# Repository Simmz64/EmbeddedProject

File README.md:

# EmbeddedProject
Project course in embedded systems

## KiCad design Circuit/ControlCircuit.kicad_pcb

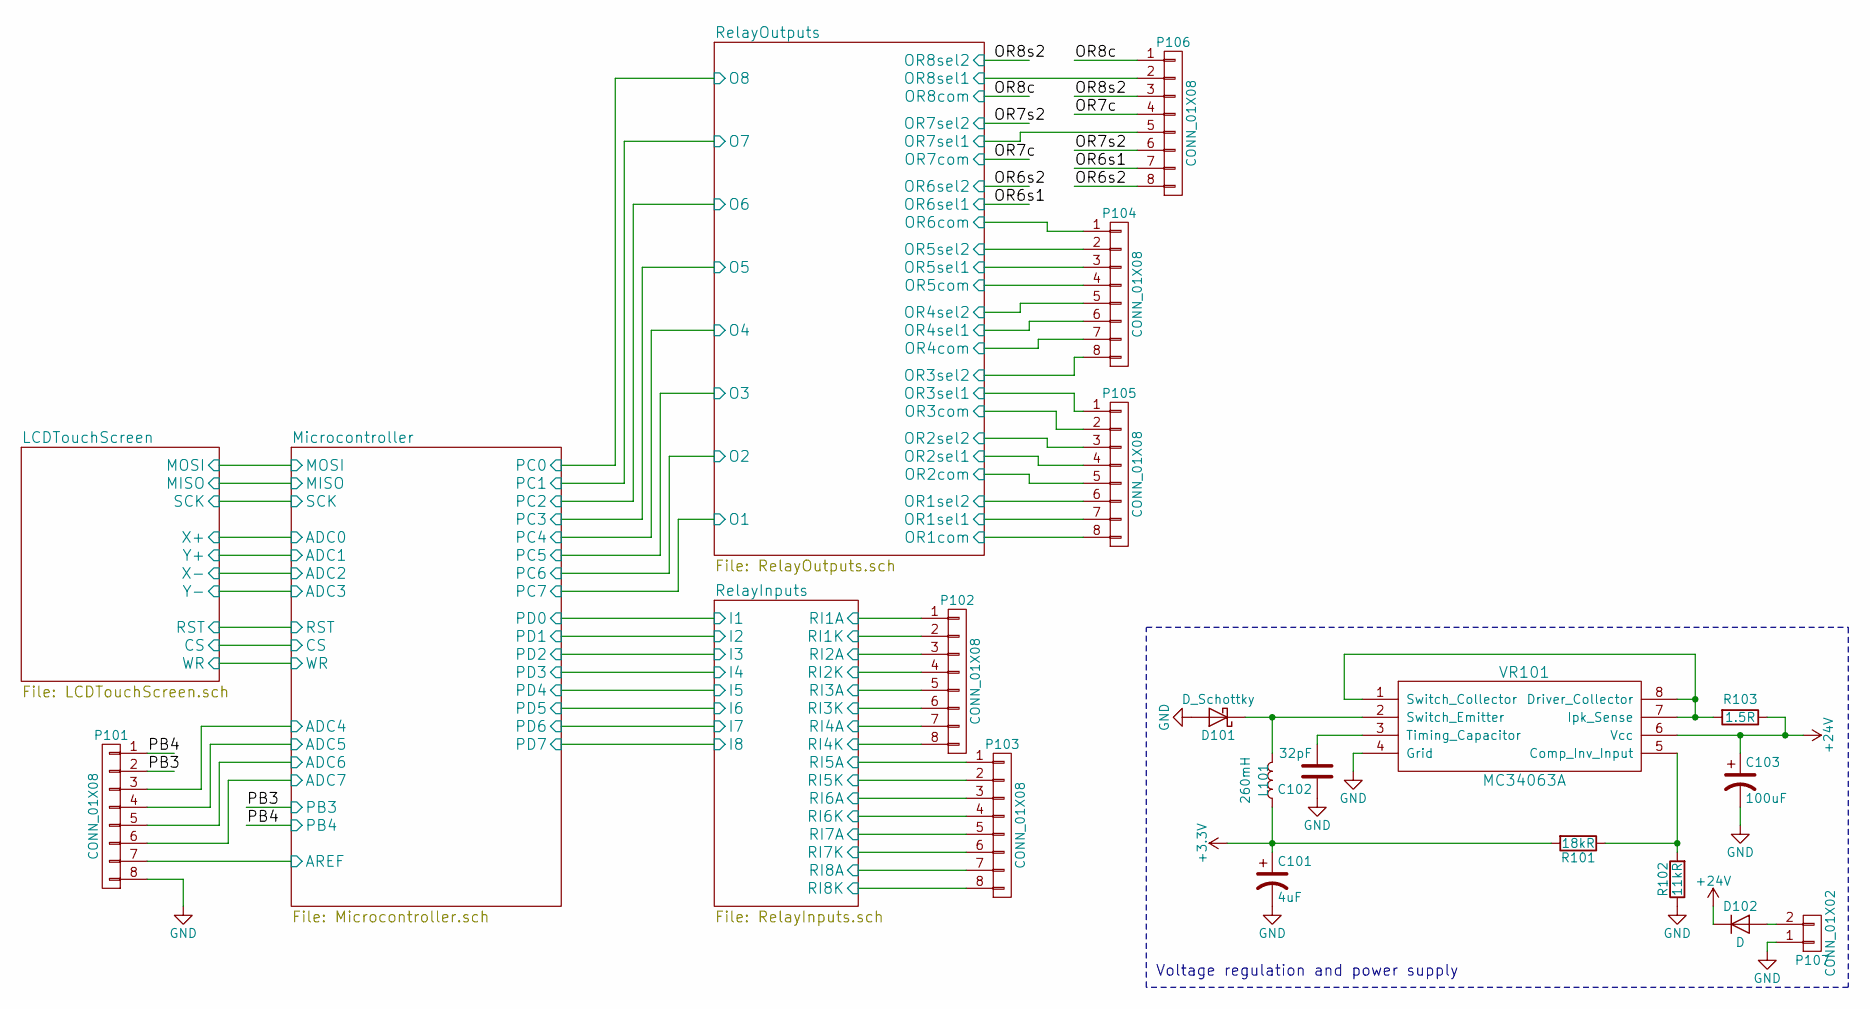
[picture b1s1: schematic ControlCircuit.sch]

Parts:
C101: 4uF; C_1206
C102: 32pF; C_0805
C103: 100uF; C_0805
D101: D_Schottky; D_MiniMELF_Standard
D102: D; D_MELF_Standard
L101: 260mH; Inductor_Wurth_HCI-7050
P101, P102, P103, P104, P105, P106: CONN_01X08; TerminalBlock_Pheonix_MKDS1.5-8pol
P107: CONN_01X02; TerminalBlock_Pheonix_MKDS1.5-2pol
R101: 18kR; R_0805
R102: 11kR; R_0805
R103: 1.5R; R_0805
VR101: MC34063A; SOIC-8_3.9x4.9mm_Pitch1.27mm

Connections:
+3V3: C101.1, L101.1, R101.2; also elsewhere on the board
+24V: C103.1, D102.1 (K), R103.1, VR101.6 (Vcc); also elsewhere on the board
/Microcontroller/ADC4: P101.3; also elsewhere on the board
/Microcontroller/ADC5: P101.4; also elsewhere on the board
/Microcontroller/ADC6: P101.5; also elsewhere on the board
/Microcontroller/ADC7: P101.6; also elsewhere on the board
/Microcontroller/AREF: P101.7; also elsewhere on the board
/OR6s1: P106.7; also elsewhere on the board
/OR6s2: P106.8; also elsewhere on the board
/OR7c: P106.4; also elsewhere on the board
/OR7s2: P106.6; also elsewhere on the board
/OR8c: P106.1; also elsewhere on the board
/OR8s2: P106.3; also elsewhere on the board
/PB3: P101.2; also elsewhere on the board
/PB4: P101.1; also elsewhere on the board
/RelayInputs/RI1A: P102.1; also elsewhere on the board
/RelayInputs/RI1K: P102.2; also elsewhere on the board
/RelayInputs/RI2A: P102.3; also elsewhere on the board
/RelayInputs/RI2K: P102.4; also elsewhere on the board
/RelayInputs/RI3A: P102.5; also elsewhere on the board
/RelayInputs/RI3K: P102.6; also elsewhere on the board
/RelayInputs/RI4A: P102.7; also elsewhere on the board
/RelayInputs/RI4K: P102.8; also elsewhere on the board
/RelayInputs/RI5A: P103.1; also elsewhere on the board
/RelayInputs/RI5K: P103.2; also elsewhere on the board
/RelayInputs/RI6A: P103.3; also elsewhere on the board
/RelayInputs/RI6K: P103.4; also elsewhere on the board
/RelayInputs/RI7A: P103.5; also elsewhere on the board
/RelayInputs/RI7K: P103.6; also elsewhere on the board
/RelayInputs/RI8A: P103.7; also elsewhere on the board
/RelayInputs/RI8K: P103.8; also elsewhere on the board
/RelayOutputs/OR1com: P105.8; also elsewhere on the board
/RelayOutputs/OR1sel1: P105.7; also elsewhere on the board
/RelayOutputs/OR1sel2: P105.6; also elsewhere on the board
/RelayOutputs/OR2com: P105.5; also elsewhere on the board
/RelayOutputs/OR2sel1: P105.4; also elsewhere on the board
/RelayOutputs/OR2sel2: P105.3; also elsewhere on the board
/RelayOutputs/OR3com: P105.2; also elsewhere on the board
/RelayOutputs/OR3sel1: P105.1; also elsewhere on the board
/RelayOutputs/OR3sel2: P104.8; also elsewhere on the board
/RelayOutputs/OR4com: P104.7; also elsewhere on the board
/RelayOutputs/OR4sel1: P104.6; also elsewhere on the board
/RelayOutputs/OR4sel2: P104.5; also elsewhere on the board
/RelayOutputs/OR5com: P104.4; also elsewhere on the board
/RelayOutputs/OR5sel1: P104.3; also elsewhere on the board
/RelayOutputs/OR5sel2: P104.2; also elsewhere on the board
/RelayOutputs/OR6com: P104.1; also elsewhere on the board
/RelayOutputs/OR7sel1: P106.5; also elsewhere on the board
/RelayOutputs/OR8sel1: P106.2; also elsewhere on the board
GND: C101.2, C102.1, C103.2, D101.2 (A), P101.8, P107.1, R102.1, VR101.4 (Grid); also elsewhere on the board
unnamed: C102.2, VR101.3 (Timing_Capacitor)
unnamed: D101.1 (K), L101.2, VR101.2 (Switch_Emitter)
unnamed: D102.2 (A), P107.2
unnamed: R101.1, R102.2, VR101.5 (Comp_Inv_Input)
unnamed: R103.2, VR101.1 (Switch_Collector), VR101.7 (Ipk_Sense), VR101.8 (Driver_Collector)

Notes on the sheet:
Voltage regulation and power supply

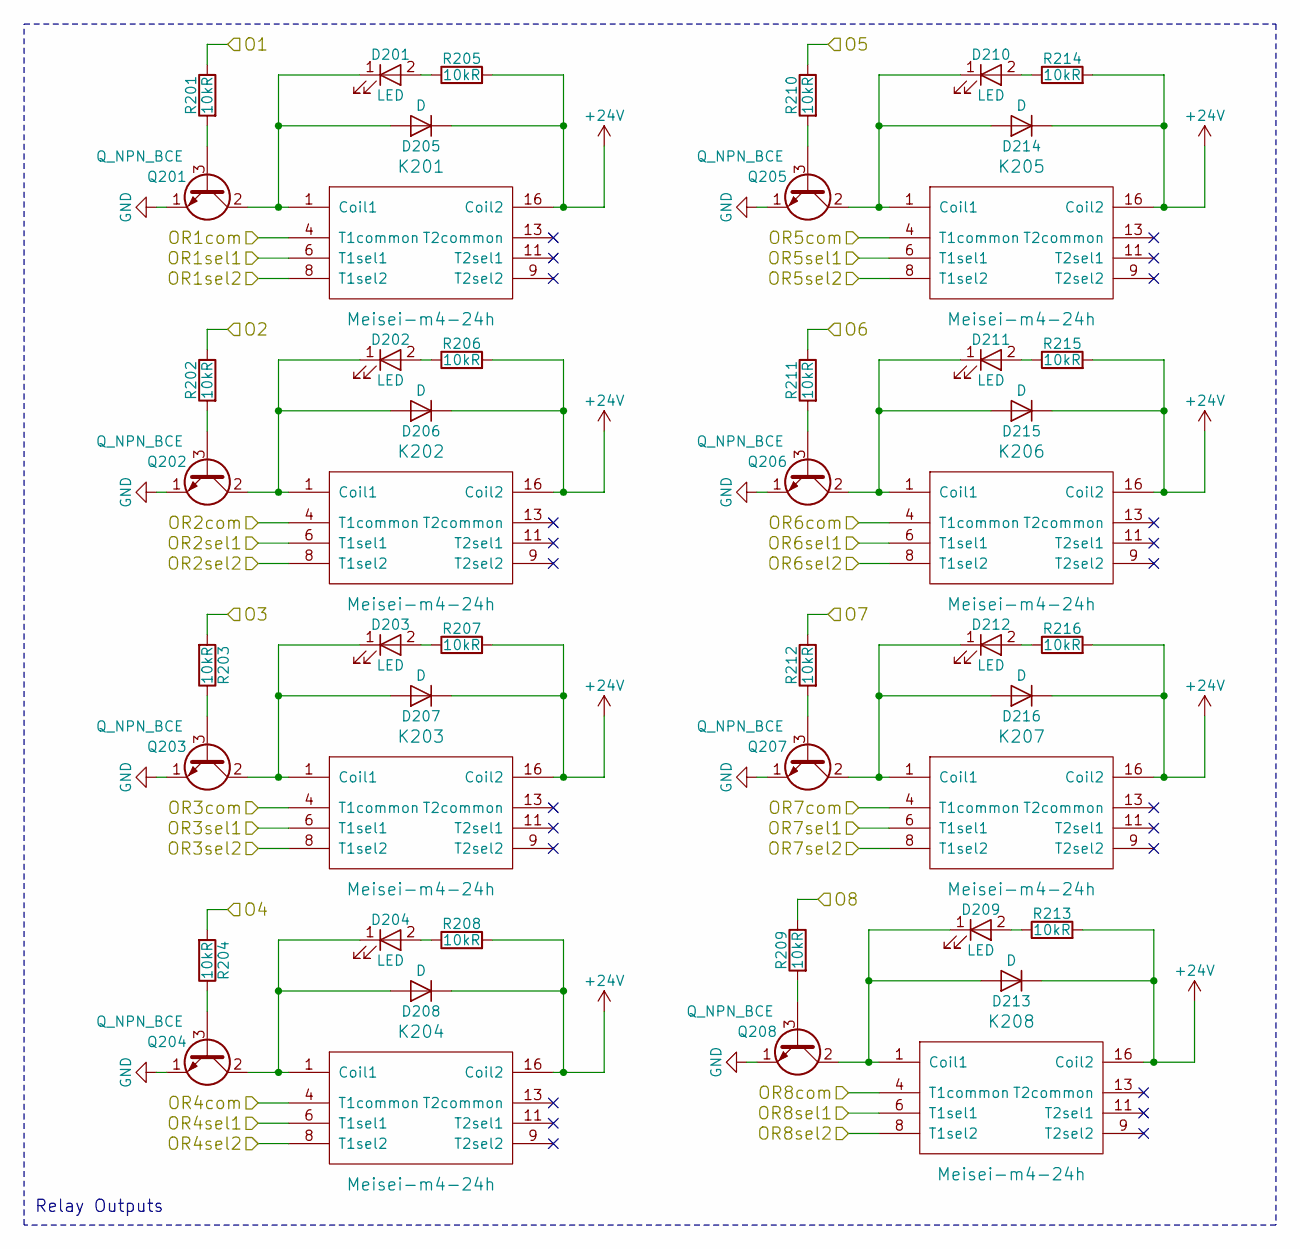
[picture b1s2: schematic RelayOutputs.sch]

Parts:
D201, D202, D203, D204, D209, D210, D211, D212: LED; C_0805
D205, D206, D207, D208, D213, D214, D215, D216: D; D_MiniMELF_Standard
K201, K202, K203, K204, K205, K206, K207, K208: Meisei-m4-24h
Q201, Q202, Q203, Q204, Q205, Q206, Q207, Q208: Q_NPN_BCE; MMBT3904
R201, R202, R203, R204, R205, R206, R207, R208, R209, R210, R211, R212, R213, R214, R215, R216: 10kR; R_0805

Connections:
+24V: D205.1 (K), D206.1 (K), D207.1 (K), D208.1 (K), D213.1 (K), D214.1 (K), D215.1 (K), D216.1 (K), K201.16 (Coil2), K202.16 (Coil2), K203.16 (Coil2), K204.16 (Coil2), K205.16 (Coil2), K206.16 (Coil2), K207.16 (Coil2), K208.16 (Coil2), R205.2, R206.2, R207.2, R208.2, R213.2, R214.2, R215.2, R216.2; also elsewhere on the board
/OR6s1: K206.6 (T1sel1); also elsewhere on the board
/OR6s2: K206.8 (T1sel2); also elsewhere on the board
/OR7c: K207.4 (T1common); also elsewhere on the board
/OR7s2: K207.8 (T1sel2); also elsewhere on the board
/OR8c: K208.4 (T1common); also elsewhere on the board
/OR8s2: K208.8 (T1sel2); also elsewhere on the board
/RelayOutputs/O1: R201.1; also elsewhere on the board
/RelayOutputs/O2: R202.1; also elsewhere on the board
/RelayOutputs/O3: R203.2; also elsewhere on the board
/RelayOutputs/O4: R204.2; also elsewhere on the board
/RelayOutputs/O5: R210.1; also elsewhere on the board
/RelayOutputs/O6: R211.1; also elsewhere on the board
/RelayOutputs/O7: R212.1; also elsewhere on the board
/RelayOutputs/O8: R209.1; also elsewhere on the board
/RelayOutputs/OR1com: K201.4 (T1common); also elsewhere on the board
/RelayOutputs/OR1sel1: K201.6 (T1sel1); also elsewhere on the board
/RelayOutputs/OR1sel2: K201.8 (T1sel2); also elsewhere on the board
/RelayOutputs/OR2com: K202.4 (T1common); also elsewhere on the board
/RelayOutputs/OR2sel1: K202.6 (T1sel1); also elsewhere on the board
/RelayOutputs/OR2sel2: K202.8 (T1sel2); also elsewhere on the board
/RelayOutputs/OR3com: K203.4 (T1common); also elsewhere on the board
/RelayOutputs/OR3sel1: K203.6 (T1sel1); also elsewhere on the board
/RelayOutputs/OR3sel2: K203.8 (T1sel2); also elsewhere on the board
/RelayOutputs/OR4com: K204.4 (T1common); also elsewhere on the board
/RelayOutputs/OR4sel1: K204.6 (T1sel1); also elsewhere on the board
/RelayOutputs/OR4sel2: K204.8 (T1sel2); also elsewhere on the board
/RelayOutputs/OR5com: K205.4 (T1common); also elsewhere on the board
/RelayOutputs/OR5sel1: K205.6 (T1sel1); also elsewhere on the board
/RelayOutputs/OR5sel2: K205.8 (T1sel2); also elsewhere on the board
/RelayOutputs/OR6com: K206.4 (T1common); also elsewhere on the board
/RelayOutputs/OR7sel1: K207.6 (T1sel1); also elsewhere on the board
/RelayOutputs/OR8sel1: K208.6 (T1sel1); also elsewhere on the board
GND: Q201.1 (E), Q202.1 (E), Q203.1 (E), Q204.1 (E), Q205.1 (E), Q206.1 (E), Q207.1 (E), Q208.1 (E); also elsewhere on the board
unnamed: D201.1 (K), D205.2 (A), K201.1 (Coil1), Q201.2 (C)
unnamed: D201.2 (A), R205.1
unnamed: D202.1 (K), D206.2 (A), K202.1 (Coil1), Q202.2 (C)
unnamed: D202.2 (A), R206.1
unnamed: D203.1 (K), D207.2 (A), K203.1 (Coil1), Q203.2 (C)
unnamed: D203.2 (A), R207.1
unnamed: D204.1 (K), D208.2 (A), K204.1 (Coil1), Q204.2 (C)
unnamed: D204.2 (A), R208.1
unnamed: D209.1 (K), D213.2 (A), K208.1 (Coil1), Q208.2 (C)
unnamed: D209.2 (A), R213.1
unnamed: D210.1 (K), D214.2 (A), K205.1 (Coil1), Q205.2 (C)
unnamed: D210.2 (A), R214.1
unnamed: D211.1 (K), D215.2 (A), K206.1 (Coil1), Q206.2 (C)
unnamed: D211.2 (A), R215.1
unnamed: D212.1 (K), D216.2 (A), K207.1 (Coil1), Q207.2 (C)
unnamed: D212.2 (A), R216.1
unnamed: Q201.3 (B), R201.2
unnamed: Q202.3 (B), R202.2
unnamed: Q203.3 (B), R203.1
unnamed: Q204.3 (B), R204.1
unnamed: Q205.3 (B), R210.2
unnamed: Q206.3 (B), R211.2
unnamed: Q207.3 (B), R212.2
unnamed: Q208.3 (B), R209.2

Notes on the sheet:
Relay Outputs

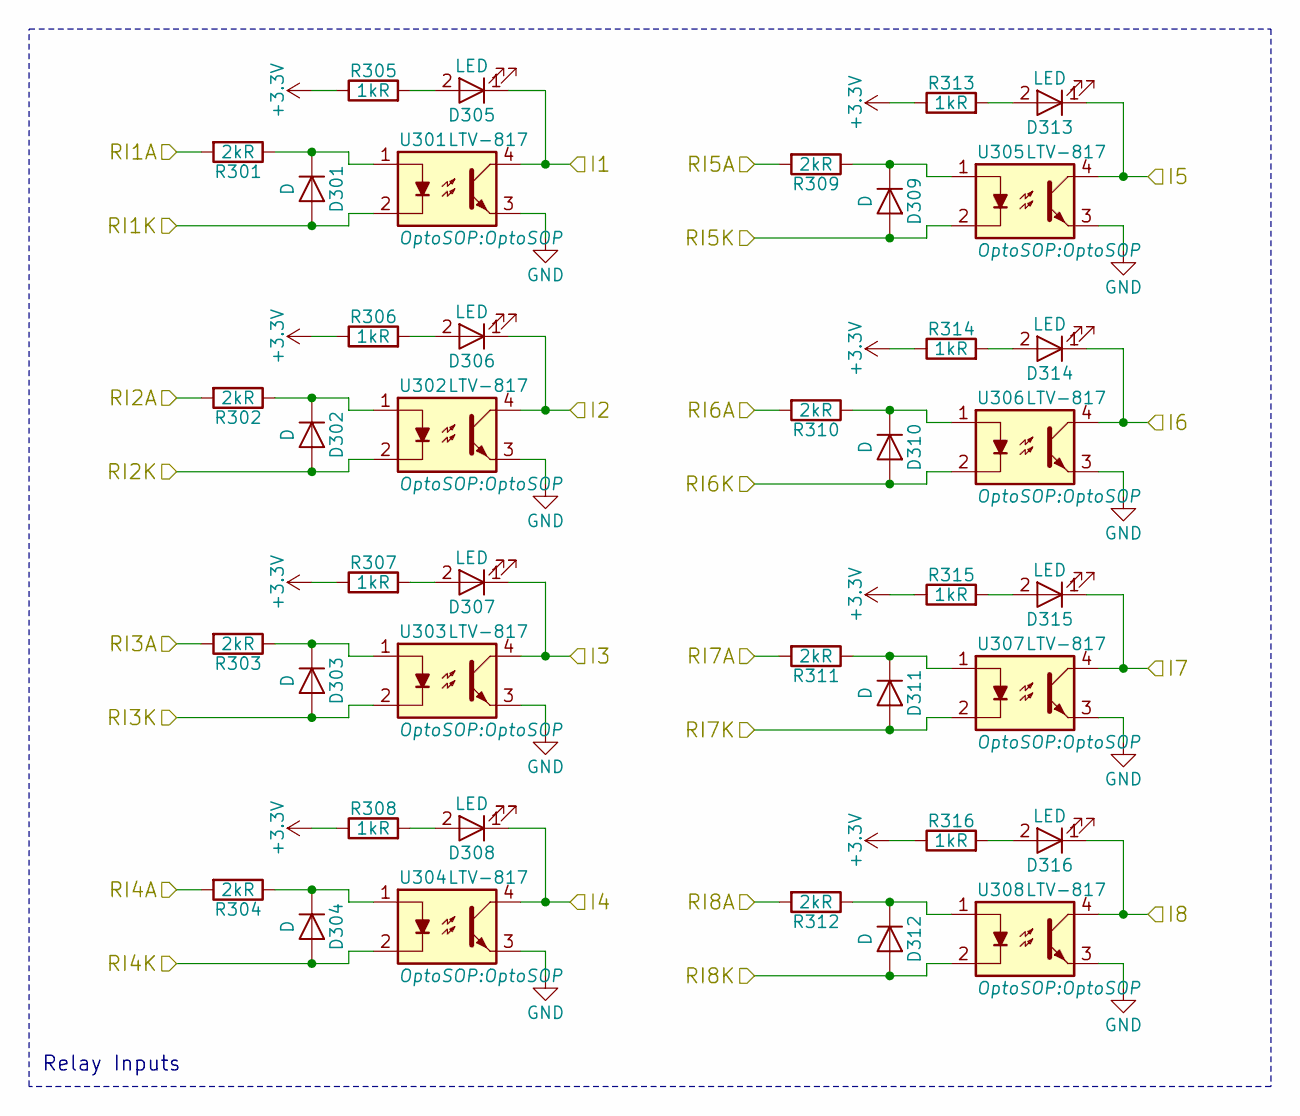
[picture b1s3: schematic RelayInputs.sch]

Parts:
D301, D302, D303, D304, D309, D310, D311, D312: D; D_MiniMELF_Standard
D305, D306, D307, D308, D313, D314, D315, D316: LED; C_0805
R301, R302, R303, R304, R309, R310, R311, R312: 2kR; R_0805
R305, R306, R307, R308, R313, R314, R315, R316: 1kR; R_0805
U301, U302, U303, U304, U305, U306, U307, U308: LTV-817; OptoSOP

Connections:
+3V3: R305.1, R306.1, R307.1, R308.1, R313.1, R314.1, R315.1, R316.1; also elsewhere on the board
/RelayInputs/I1: D305.1 (K), U301.4; also elsewhere on the board
/RelayInputs/I2: D306.1 (K), U302.4; also elsewhere on the board
/RelayInputs/I3: D307.1 (K), U303.4; also elsewhere on the board
/RelayInputs/I4: D308.1 (K), U304.4; also elsewhere on the board
/RelayInputs/I5: D313.1 (K), U305.4; also elsewhere on the board
/RelayInputs/I6: D314.1 (K), U306.4; also elsewhere on the board
/RelayInputs/I7: D315.1 (K), U307.4; also elsewhere on the board
/RelayInputs/I8: D316.1 (K), U308.4; also elsewhere on the board
/RelayInputs/RI1A: R301.2; also elsewhere on the board
/RelayInputs/RI1K: D301.2 (A), U301.2; also elsewhere on the board
/RelayInputs/RI2A: R302.2; also elsewhere on the board
/RelayInputs/RI2K: D302.2 (A), U302.2; also elsewhere on the board
/RelayInputs/RI3A: R303.2; also elsewhere on the board
/RelayInputs/RI3K: D303.2 (A), U303.2; also elsewhere on the board
/RelayInputs/RI4A: R304.2; also elsewhere on the board
/RelayInputs/RI4K: D304.2 (A), U304.2; also elsewhere on the board
/RelayInputs/RI5A: R309.2; also elsewhere on the board
/RelayInputs/RI5K: D309.2 (A), U305.2; also elsewhere on the board
/RelayInputs/RI6A: R310.2; also elsewhere on the board
/RelayInputs/RI6K: D310.2 (A), U306.2; also elsewhere on the board
/RelayInputs/RI7A: R311.2; also elsewhere on the board
/RelayInputs/RI7K: D311.2 (A), U307.2; also elsewhere on the board
/RelayInputs/RI8A: R312.2; also elsewhere on the board
/RelayInputs/RI8K: D312.2 (A), U308.2; also elsewhere on the board
GND: U301.3, U302.3, U303.3, U304.3, U305.3, U306.3, U307.3, U308.3; also elsewhere on the board
unnamed: D301.1 (K), R301.1, U301.1
unnamed: D302.1 (K), R302.1, U302.1
unnamed: D303.1 (K), R303.1, U303.1
unnamed: D304.1 (K), R304.1, U304.1
unnamed: D305.2 (A), R305.2
unnamed: D306.2 (A), R306.2
unnamed: D307.2 (A), R307.2
unnamed: D308.2 (A), R308.2
unnamed: D309.1 (K), R309.1, U305.1
unnamed: D310.1 (K), R310.1, U306.1
unnamed: D311.1 (K), R311.1, U307.1
unnamed: D312.1 (K), R312.1, U308.1
unnamed: D313.2 (A), R313.2
unnamed: D314.2 (A), R314.2
unnamed: D315.2 (A), R315.2
unnamed: D316.2 (A), R316.2

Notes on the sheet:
Relay Inputs

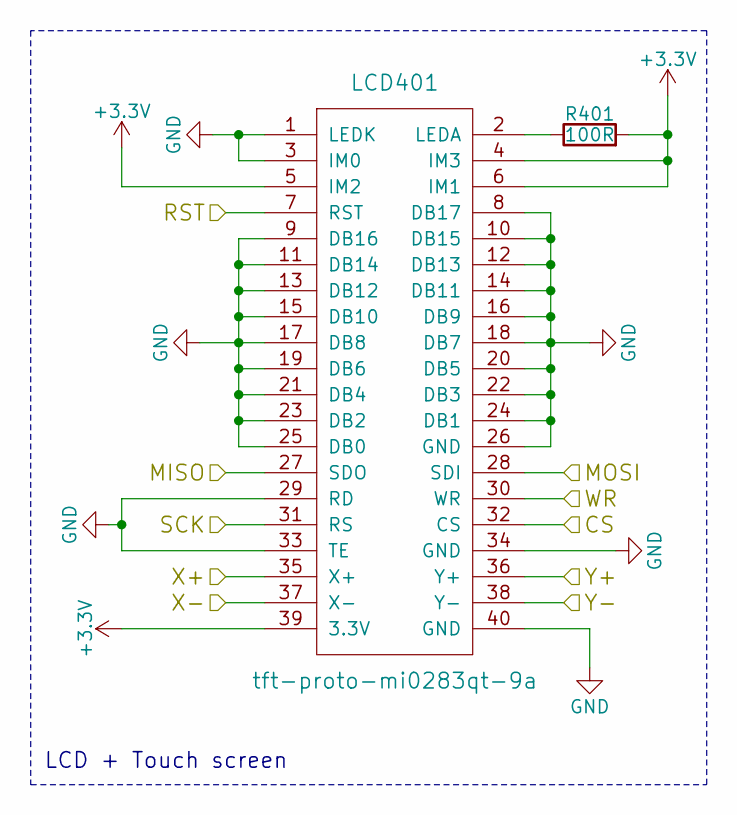
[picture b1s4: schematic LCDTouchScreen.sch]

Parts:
LCD401: tft-proto-mi0283qt-9a; Pin_Header_Straight_2x20_Pitch2.54mm
R401: 100R; R_0805

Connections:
+3V3: LCD401.4 (IM3), LCD401.5 (IM2), LCD401.6 (IM1), LCD401.39 (3.3V), R401.2; also elsewhere on the board
/LCDTouchScreen/CS: LCD401.32 (CS); also elsewhere on the board
/LCDTouchScreen/MISO: LCD401.27 (SDO); also elsewhere on the board
/LCDTouchScreen/MOSI: LCD401.28 (SDI); also elsewhere on the board
/LCDTouchScreen/RST: LCD401.7 (RST); also elsewhere on the board
/LCDTouchScreen/SCK: LCD401.31 (RS); also elsewhere on the board
/LCDTouchScreen/WR: LCD401.30 (WR); also elsewhere on the board
/Microcontroller/ADC0: LCD401.35 (X+); also elsewhere on the board
/Microcontroller/ADC1: LCD401.36 (Y+); also elsewhere on the board
/Microcontroller/ADC2: LCD401.37 (X-); also elsewhere on the board
/Microcontroller/ADC3: LCD401.38 (Y-); also elsewhere on the board
GND: LCD401.1 (LEDK), LCD401.3 (IM0), LCD401.8 (DB17), LCD401.9 (DB16), LCD401.10 (DB15), LCD401.11 (DB14), LCD401.12 (DB13), LCD401.13 (DB12), LCD401.14 (DB11), LCD401.15 (DB10), LCD401.16 (DB9), LCD401.17 (DB8), LCD401.18 (DB7), LCD401.19 (DB6), LCD401.20 (DB5), LCD401.21 (DB4), LCD401.22 (DB3), LCD401.23 (DB2), LCD401.24 (DB1), LCD401.25 (DB0), LCD401.26 (GND), LCD401.29 (RD), LCD401.33 (TE), LCD401.34 (GND), LCD401.40 (GND); also elsewhere on the board
unnamed: LCD401.2 (LEDA), R401.1

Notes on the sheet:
LCD + Touch screen

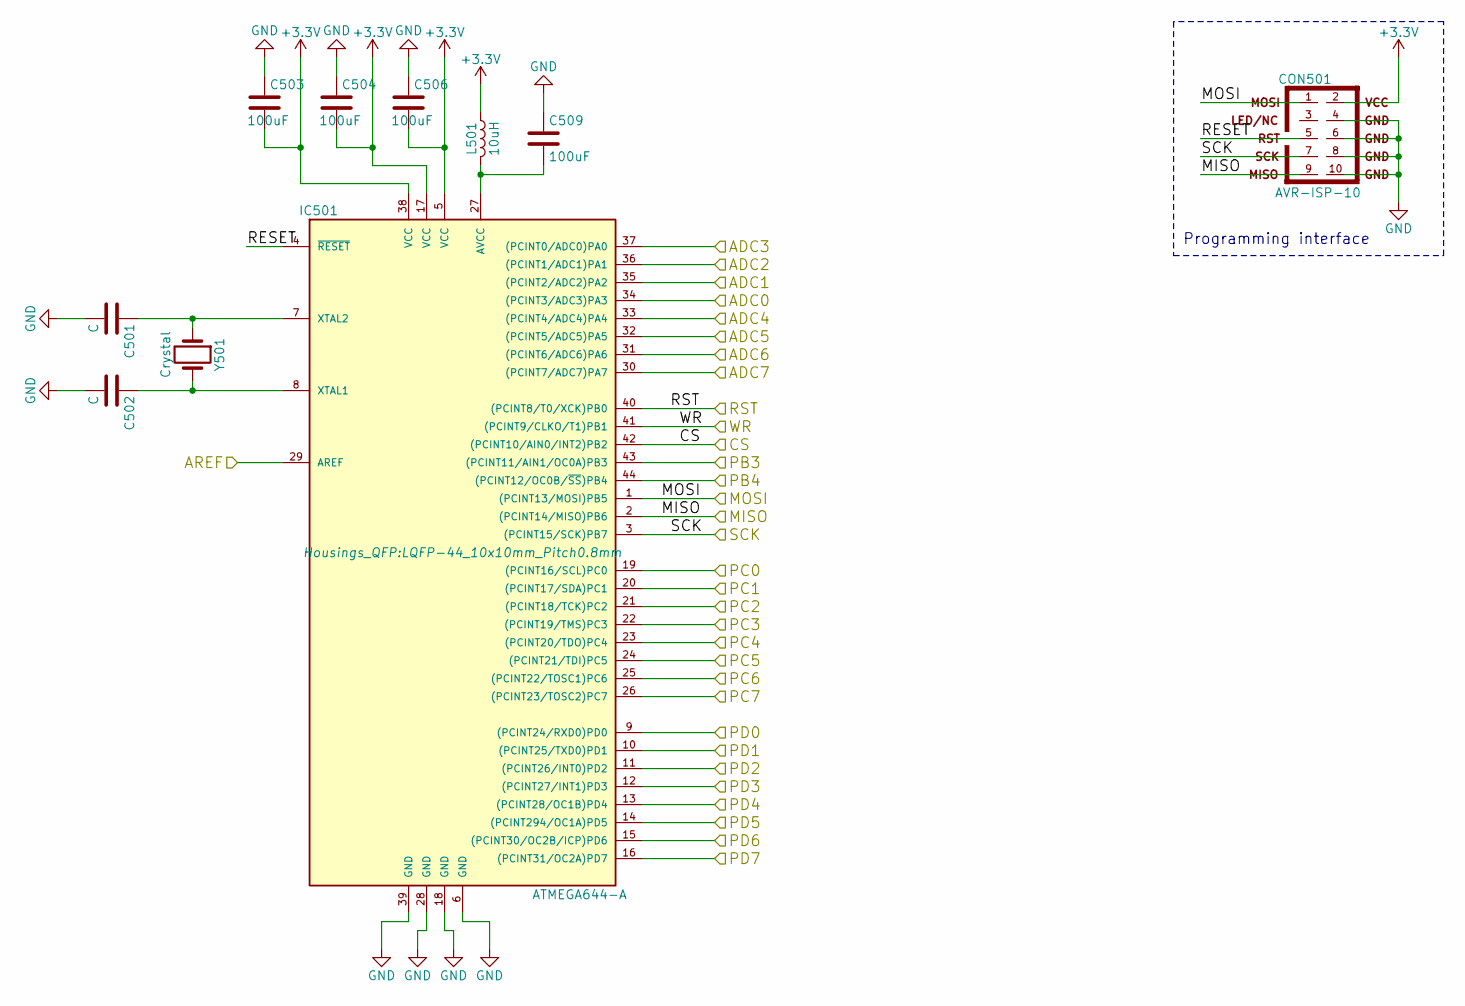
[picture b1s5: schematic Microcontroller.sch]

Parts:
C501, C502: C; C_0805
C503, C504, C506, C509: 100uF; C_0805
CON501: AVR-ISP-10; IDC_Header_Straight_10pins
IC501: ATMEGA644-A; LQFP-44_10x10mm_Pitch0.8mm
L501: 10uH; C_1206
Y501: Crystal; Crystal_HC49-U_Vertical

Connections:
+3V3: C503.2, C504.2, C506.2, CON501.2, IC501.5 (VCC), IC501.17 (VCC), IC501.38 (VCC), L501.1; also elsewhere on the board
/LCDTouchScreen/CS: IC501.42 ((PCINT10/AIN0/INT2)PB2); also elsewhere on the board
/LCDTouchScreen/MISO: CON501.9, IC501.2 ((PCINT14/MISO)PB6); also elsewhere on the board
/LCDTouchScreen/MOSI: CON501.1, IC501.1 ((PCINT13/MOSI)PB5); also elsewhere on the board
/LCDTouchScreen/RST: IC501.40 ((PCINT8/T0/XCK)PB0); also elsewhere on the board
/LCDTouchScreen/SCK: CON501.7, IC501.3 ((PCINT15/SCK)PB7); also elsewhere on the board
/LCDTouchScreen/WR: IC501.41 ((PCINT9/CLKO/T1)PB1); also elsewhere on the board
/Microcontroller/ADC0: IC501.34 ((PCINT3/ADC3)PA3); also elsewhere on the board
/Microcontroller/ADC1: IC501.35 ((PCINT2/ADC2)PA2); also elsewhere on the board
/Microcontroller/ADC2: IC501.36 ((PCINT1/ADC1)PA1); also elsewhere on the board
/Microcontroller/ADC3: IC501.37 ((PCINT0/ADC0)PA0); also elsewhere on the board
/Microcontroller/ADC4: IC501.33 ((PCINT4/ADC4)PA4); also elsewhere on the board
/Microcontroller/ADC5: IC501.32 ((PCINT5/ADC5)PA5); also elsewhere on the board
/Microcontroller/ADC6: IC501.31 ((PCINT6/ADC6)PA6); also elsewhere on the board
/Microcontroller/ADC7: IC501.30 ((PCINT7/ADC7)PA7); also elsewhere on the board
/Microcontroller/AREF: IC501.29 (AREF); also elsewhere on the board
/Microcontroller/RESET: CON501.5, IC501.4 (~RESET)
/PB3: IC501.43 ((PCINT11/AIN1/OC0A)PB3); also elsewhere on the board
/PB4: IC501.44 ((PCINT12/OC0B/~SS~)PB4); also elsewhere on the board
/RelayInputs/I1: IC501.9 ((PCINT24/RXD0)PD0); also elsewhere on the board
/RelayInputs/I2: IC501.10 ((PCINT25/TXD0)PD1); also elsewhere on the board
/RelayInputs/I3: IC501.11 ((PCINT26/INT0)PD2); also elsewhere on the board
/RelayInputs/I4: IC501.12 ((PCINT27/INT1)PD3); also elsewhere on the board
/RelayInputs/I5: IC501.13 ((PCINT28/OC1B)PD4); also elsewhere on the board
/RelayInputs/I6: IC501.14 ((PCINT294/OC1A)PD5); also elsewhere on the board
/RelayInputs/I7: IC501.15 ((PCINT30/OC2B/ICP)PD6); also elsewhere on the board
/RelayInputs/I8: IC501.16 ((PCINT31/OC2A)PD7); also elsewhere on the board
/RelayOutputs/O1: IC501.26 ((PCINT23/TOSC2)PC7); also elsewhere on the board
/RelayOutputs/O2: IC501.25 ((PCINT22/TOSC1)PC6); also elsewhere on the board
/RelayOutputs/O3: IC501.24 ((PCINT21/TDI)PC5); also elsewhere on the board
/RelayOutputs/O4: IC501.23 ((PCINT20/TDO)PC4); also elsewhere on the board
/RelayOutputs/O5: IC501.22 ((PCINT19/TMS)PC3); also elsewhere on the board
/RelayOutputs/O6: IC501.21 ((PCINT18/TCK)PC2); also elsewhere on the board
/RelayOutputs/O7: IC501.20 ((PCINT17/SDA)PC1); also elsewhere on the board
/RelayOutputs/O8: IC501.19 ((PCINT16/SCL)PC0); also elsewhere on the board
GND: C501.2, C502.2, C503.1, C504.1, C506.1, C509.1, CON501.4, CON501.6, CON501.8, CON501.10, IC501.6 (GND), IC501.18 (GND), IC501.28 (GND), IC501.39 (GND); also elsewhere on the board
unnamed: C501.1, IC501.7 (XTAL2), Y501.1
unnamed: C502.1, IC501.8 (XTAL1), Y501.2
unnamed: C509.2, IC501.27 (AVCC), L501.2

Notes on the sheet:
Programming interface

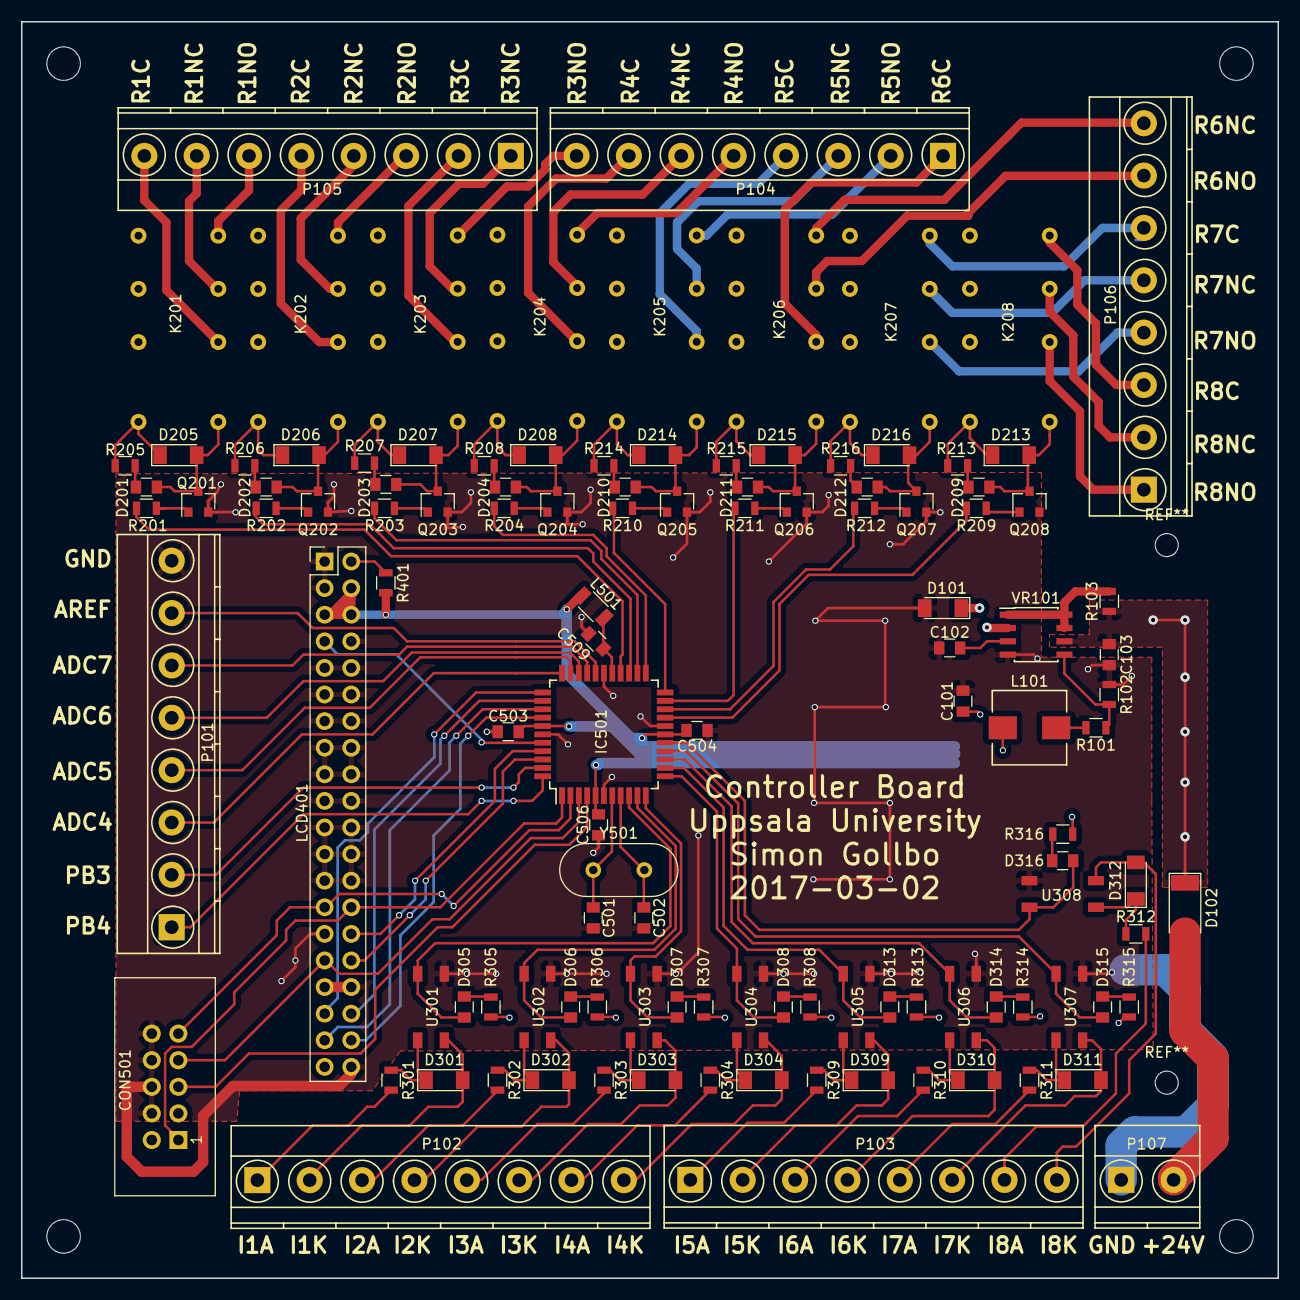
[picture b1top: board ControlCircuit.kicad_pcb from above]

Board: 2 copper layers, 120.0 x 120.0 mm, 117 parts (0 on the bottom side), 126 nets.

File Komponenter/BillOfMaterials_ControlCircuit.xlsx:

comp_id | value | footprint | tstamp | ref | Antal | Komponent | Antal | Kommentar
5 | 32pF | Capacitors_SMD:C_0805 | 58ADC3B5 | C102 | 1 | Capacitors_SMD:C_0805 | 25
7 | 4uF | Capacitors_SMD:C_0805 | 58ADC46F | C101 | 1 | Capacitors_SMD:C_1206 | 1
8 | 100uF | Capacitors_SMD:C_0805 | 58ADC4C2 | C103 | 1 | Connectors:IDC_Header_Straight_10pins | 1
50 | LED | Capacitors_SMD:C_0805 | 58B75E5F | D209 |  | Connectors_Terminal_Blocks:TerminalBlock_Pheonix_MKDS1.5-2pol | 1
52 | LED | Capacitors_SMD:C_0805 | 58B77770 | D212 |  | Connectors_Terminal_Blocks:TerminalBlock_Pheonix_MKDS1.5-8pol | 6
54 | LED | Capacitors_SMD:C_0805 | 58B79DE6 | D204 |  | Crystals:Crystal_HC49-U_Vertical | 1
56 | LED | Capacitors_SMD:C_0805 | 58B79F0F | D203 |  | Diodes_SMD:D_MELF_Standard | 1
58 | LED | Capacitors_SMD:C_0805 | 58B7A016 | D211 |  | Diodes_SMD:D_MiniMELF_Standard | 17
60 | LED | Capacitors_SMD:C_0805 | 58B7A165 | D210 |  | Housings_QFP:LQFP-44_10x10mm_Pitch0.8mm | 1
62 | LED | Capacitors_SMD:C_0805 | 58B7A28C | D202 |  | Housings_SOIC:SOIC-8_3.9x4.9mm_Pitch1.27mm | 1
64 | LED | Capacitors_SMD:C_0805 | 58B7A381 | D201 |  | Inductors:Inductor_Wurth_HCI-7050 | 1
90 | LED | Capacitors_SMD:C_0805 | 58B85306 | D305 |  | Meisei:Meisei-m4-24h | 8
92 | LED | Capacitors_SMD:C_0805 | 58B853B4 | D307 |  | MMBT3904:MMBT3904 | 8
94 | LED | Capacitors_SMD:C_0805 | 58B85438 | D306 |  | OptoSOP:OptoSOP | 8 | HCPL-181-06BE
96 | LED | Capacitors_SMD:C_0805 | 58B854CE | D308 |  | Pin_Headers:Pin_Header_Straight_2x20_Pitch2.54mm | 1
98 | LED | Capacitors_SMD:C_0805 | 58B85556 | D313 |  | Resistors_SMD:R_0805 | 36
100 | LED | Capacitors_SMD:C_0805 | 58B85620 | D314
102 | LED | Capacitors_SMD:C_0805 | 58B856F8 | D315 | Antal
104 | LED | Capacitors_SMD:C_0805 | 58B857BA | D316 | 16
111 | 27pF | Capacitors_SMD:C_0805 | 58AFE5FE | C501 | 1
112 | 27pF | Capacitors_SMD:C_0805 | 58AFE643 | C502 | 1
114 | 100uF | Capacitors_SMD:C_0805 | 58B7F754 | C509
115 | 100uF | Capacitors_SMD:C_0805 | 58B7F7C6 | C503
116 | 100uF | Capacitors_SMD:C_0805 | 58B819B7 | C504 | Antal
117 | 100uF | Capacitors_SMD:C_0805 | 58B819EA | C506 | 4
113 | 10uH | Capacitors_SMD:C_1206 | 58B7F6E5 | L501 | 1
109 | AVR-ISP-10 | Connectors:IDC_Header_Straight_10pins | 58AFDD08 | CON501 | 1
10 | CONN_01X02 | Connectors_Terminal_Blocks:TerminalBlock_Pheonix_MKDS1.5-2pol | 58B072B8 | P107 | 1
11 | CONN_01X08 | Connectors_Terminal_Blocks:TerminalBlock_Pheonix_MKDS1.5-8pol | 58B3B87B | P102
12 | CONN_01X08 | Connectors_Terminal_Blocks:TerminalBlock_Pheonix_MKDS1.5-8pol | 58B3CE21 | P105
13 | CONN_01X08 | Connectors_Terminal_Blocks:TerminalBlock_Pheonix_MKDS1.5-8pol | 58B3D077 | P104
14 | CONN_01X08 | Connectors_Terminal_Blocks:TerminalBlock_Pheonix_MKDS1.5-8pol | 58B3D2CE | P106
15 | CONN_01X08 | Connectors_Terminal_Blocks:TerminalBlock_Pheonix_MKDS1.5-8pol | 58B5A21E | P103 | Antal
16 | CONN_01X08 | Connectors_Terminal_Blocks:TerminalBlock_Pheonix_MKDS1.5-8pol | 58B62A9C | P101 | 6
110 | Crystal | Crystals:Crystal_HC49-U_Vertical | 58AFE5B1 | Y501 | 1
17 | D (MELF) | Diodes_SMD:D_MELF_Standard | 58BAFEB2 | D102 | 1
9 | D_Schottky | Diodes_SMD:D_MiniMELF_Standard | 58ADC506 | D101 | 1
21 | D | Diodes_SMD:D_MiniMELF_Standard | 58AE6BBC | D208
25 | D | Diodes_SMD:D_MiniMELF_Standard | 58AE898F | D214
29 | D | Diodes_SMD:D_MiniMELF_Standard | 58AE8A67 | D215
33 | D | Diodes_SMD:D_MiniMELF_Standard | 58AE8E43 | D205
37 | D | Diodes_SMD:D_MiniMELF_Standard | 58AE8E83 | D206
41 | D | Diodes_SMD:D_MiniMELF_Standard | 58AE8EC3 | D207
45 | D | Diodes_SMD:D_MiniMELF_Standard | 58B0DA2A | D216
49 | D | Diodes_SMD:D_MiniMELF_Standard | 58B0DA5D | D213
67 | D | Diodes_SMD:D_MiniMELF_Standard | 58B4FD7A | D309
70 | D | Diodes_SMD:D_MiniMELF_Standard | 58B50714 | D310
73 | D | Diodes_SMD:D_MiniMELF_Standard | 58B51C94 | D311
76 | D | Diodes_SMD:D_MiniMELF_Standard | 58B51CBB | D312
79 | D | Diodes_SMD:D_MiniMELF_Standard | 58B51EF5 | D301
82 | D | Diodes_SMD:D_MiniMELF_Standard | 58B51F1C | D302
85 | D | Diodes_SMD:D_MiniMELF_Standard | 58B51F43 | D303 | Antal
88 | D | Diodes_SMD:D_MiniMELF_Standard | 58B51F6A | D304 | 16
108 | ATMEGA644-A | Housings_QFP:LQFP-44_10x10mm_Pitch0.8mm | 58AFCD20 | IC501 | 1
1 | MC34063A | Housings_SOIC:SOIC-8_3.9x4.9mm_Pitch1.27mm | 58ADBEF0 | VR101 | 1
6 | 260mH | Inductors:Inductor_Wurth_HCI-7050 | 58ADC41A | L101 | 1
18 | Meisei-m4-24h | Meisei:Meisei-m4-24h | 58ADF9BD | K204
22 | Meisei-m4-24h | Meisei:Meisei-m4-24h | 58AE8967 | K205
26 | Meisei-m4-24h | Meisei:Meisei-m4-24h | 58AE8A3F | K206
30 | Meisei-m4-24h | Meisei:Meisei-m4-24h | 58AE8E17 | K201
34 | Meisei-m4-24h | Meisei:Meisei-m4-24h | 58AE8E57 | K202
38 | Meisei-m4-24h | Meisei:Meisei-m4-24h | 58AE8E97 | K203
42 | Meisei-m4-24h | Meisei:Meisei-m4-24h | 58B0DA07 | K207 | Antal
46 | Meisei-m4-24h | Meisei:Meisei-m4-24h | 58B0DA3A | K208 | 8
19 | Q_NPN_BCE | MMBT3904:MMBT3904 | 58ADF9C4 | Q204
23 | Q_NPN_BCE | MMBT3904:MMBT3904 | 58AE896D | Q205
27 | Q_NPN_BCE | MMBT3904:MMBT3904 | 58AE8A45 | Q206
31 | Q_NPN_BCE | MMBT3904:MMBT3904 | 58AE8E1D | Q201
35 | Q_NPN_BCE | MMBT3904:MMBT3904 | 58AE8E5D | Q202
39 | Q_NPN_BCE | MMBT3904:MMBT3904 | 58AE8E9D | Q203
43 | Q_NPN_BCE | MMBT3904:MMBT3904 | 58B0DA0D | Q207 | Antal
47 | Q_NPN_BCE | MMBT3904:MMBT3904 | 58B0DA40 | Q208 | 8
66 | HCPL-181-06BE | OptoSOP:OptoSOP | 58B4F7B2 | U305 |  | Kommentar
69 | HCPL-181-06BE | OptoSOP:OptoSOP | 58B5070E | U306 |  | Finns på Farnell och RS-components (dock i utförandet
72 | HCPL-181-06BE | OptoSOP:OptoSOP | 58B51C8E | U307 |  | HCPL-181-00BE på RS-components, men de verkar likvärdiga)
75 | HCPL-181-06BE | OptoSOP:OptoSOP | 58B51CB5 | U308
78 | HCPL-181-06BE | OptoSOP:OptoSOP | 58B51EEF | U301 |  | Har utgått ur sortimentet på Elfa
81 | HCPL-181-06BE | OptoSOP:OptoSOP | 58B51F16 | U302
84 | HCPL-181-06BE | OptoSOP:OptoSOP | 58B51F3D | U303 | Antal
87 | HCPL-181-06BE | OptoSOP:OptoSOP | 58B51F64 | U304 | 8
106 | tft-proto-mi0283qt-9a | Pin_Headers:Pin_Header_Straight_2x20_Pitch2.54mm | 58AFAB48 | LCD401 | 1
2 | 18kR | Resistors_SMD:R_0805 | 58ADBF75 | R101 | 1
3 | 11kR | Resistors_SMD:R_0805 | 58ADC02F | R102 | 1
20 | 10kR | Resistors_SMD:R_0805 | 58ADF9CB | R204
24 | 10kR | Resistors_SMD:R_0805 | 58AE8973 | R210
28 | 10kR | Resistors_SMD:R_0805 | 58AE8A4B | R211
32 | 10kR | Resistors_SMD:R_0805 | 58AE8E23 | R201
36 | 10kR | Resistors_SMD:R_0805 | 58AE8E63 | R202
40 | 10kR | Resistors_SMD:R_0805 | 58AE8EA3 | R203
44 | 10kR | Resistors_SMD:R_0805 | 58B0DA13 | R212
48 | 10kR | Resistors_SMD:R_0805 | 58B0DA46 | R209
51 | 10kR | Resistors_SMD:R_0805 | 58B75EDE | R213
53 | 10kR | Resistors_SMD:R_0805 | 58B77776 | R216
55 | 10kR | Resistors_SMD:R_0805 | 58B79DEC | R208
57 | 10kR | Resistors_SMD:R_0805 | 58B79F15 | R207
59 | 10kR | Resistors_SMD:R_0805 | 58B7A01C | R215
61 | 10kR | Resistors_SMD:R_0805 | 58B7A16B | R214
63 | 10kR | Resistors_SMD:R_0805 | 58B7A292 | R206 | Antal
65 | 10kR | Resistors_SMD:R_0805 | 58B7A387 | R205 | 16
68 | 2kR | Resistors_SMD:R_0805 | 58B4FDCB | R309
71 | 2kR | Resistors_SMD:R_0805 | 58B5071A | R310
74 | 2kR | Resistors_SMD:R_0805 | 58B51C9A | R311
77 | 2kR | Resistors_SMD:R_0805 | 58B51CC1 | R312
80 | 2kR | Resistors_SMD:R_0805 | 58B51EFB | R301
83 | 2kR | Resistors_SMD:R_0805 | 58B51F22 | R302
86 | 2kR | Resistors_SMD:R_0805 | 58B51F49 | R303 | Antal
89 | 2kR | Resistors_SMD:R_0805 | 58B51F70 | R304 | 8
91 | 1kR | Resistors_SMD:R_0805 | 58B8530C | R305
93 | 1kR | Resistors_SMD:R_0805 | 58B853BA | R307
95 | 1kR | Resistors_SMD:R_0805 | 58B8543E | R306
97 | 1kR | Resistors_SMD:R_0805 | 58B854D4 | R308
99 | 1kR | Resistors_SMD:R_0805 | 58B8555C | R313
101 | 1kR | Resistors_SMD:R_0805 | 58B85626 | R314
103 | 1kR | Resistors_SMD:R_0805 | 58B856FE | R315 | Antal
105 | 1kR | Resistors_SMD:R_0805 | 58B857C0 | R316 | 8
107 | 100R | Resistors_SMD:R_0805 | 58AFAB4F | R401 | 1
4 | 1.5R | Resistors_SMD:R_0805 | 58ADC09B | R103 | 1

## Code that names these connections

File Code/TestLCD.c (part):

/*
ATmega8, 48, 88, 168, 328

/Reset   PC6|1   28|PC5
RxD      PD0|2   27|PC4
TxD      PD1|3   26|PC3       Y-
         PD2|4   25|PC2       X-
         PD3|5   24|PC1       Y+
         PD4|6   23|PC0       X+
         Vcc|7   22|Gnd
         Gnd|8   21|Aref
         PB6|9   20|AVcc
         PB7|10  19|PB5       SCK
         PD5|11  18|PB4       MISO
         PD6|12  17|PB3       MOSI
   RST   PD7|13  16|PB2       DC
         PB0|14  15|PB1       CS
*/

#define  F_CPU 12000000UL
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
//#define rxplate

// X+ - PC0
// Y+ - PC1
// X- - PC2
// Y- - PC3

#define XP PC0
#define YP PC1
#define XM PC2
#define YM PC3

/***** Function prototypes ******/
//void init(void);
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
void init(void) {

	// Set MOSI, SCK, PB1, PB2 as output
	DDRB = (1<<PB5)|(1<<PB3) | (1<<PB1)|(1<<PB2)|(1<<PB0);
	DDRD = (1<<PD7);
	// Initialize SPI command register
	SPCR = (0<<SPIE)|(1<<SPE)|(1<<MSTR)|(1<<CPHA)|(1<<CPOL)|(0<<SPR1)|(0<<SPR0);
	SPSR = (1<<SPI2X);
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}

void cs_high(void) {
	PORTB |= (1<<PB1);
}

void cs_low(void) {
	PORTB &= (0xFF ^ (1<<PB1));
}

void dc_high(void) {
	PORTB |= (1<<PB2);
}

void dc_low(void) {
	PORTB &= (0xFF ^ (1<<PB2));
}

void rst_high(void) {
	PORTD |= (1<<PD7);
}

void rst_low(void) {
	PORTD &= (0xFF ^ (1<<PD7));
}

void wr_cmd(unsigned char cmd) {
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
